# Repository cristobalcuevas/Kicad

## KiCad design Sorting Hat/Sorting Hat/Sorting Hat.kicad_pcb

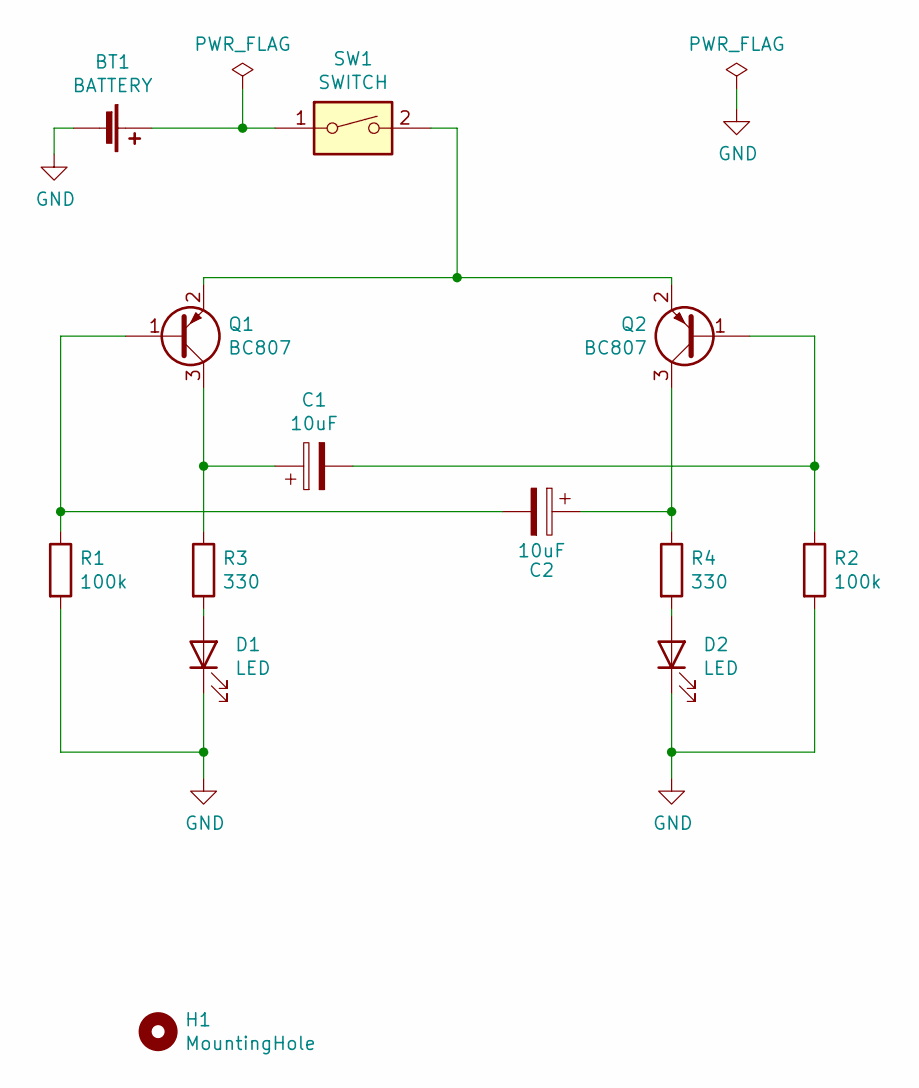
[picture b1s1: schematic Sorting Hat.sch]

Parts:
BT1: BATTERY; MPD_BK-912-TR
C1, C2: 10uF; CP_Elec_4x5.4
D1, D2: LED; D_1206_3216Metric_Pad1.42x1.75mm_HandSolder
H1: MountingHole; MountingHole_2.2mm_M2
Q1, Q2: BC807; SOT-23
R1, R2: 100k; R_1206_3216Metric_Pad1.42x1.75mm_HandSolder
R3, R4: 330; R_1206_3216Metric_Pad1.42x1.75mm_HandSolder
SW1: SWITCH; A6S-1104-H

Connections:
GND: BT1.2 (-), D1.1 (K), D2.1 (K), R1.2, R2.2
unnamed: BT1.1 (+), SW1.1
unnamed: C1.1, Q1.3 (C), R3.1
unnamed: C1.2, Q2.1 (B), R2.1
unnamed: C2.1, Q2.3 (C), R4.1
unnamed: C2.2, Q1.1 (B), R1.1
unnamed: D1.2 (A), R3.2
unnamed: D2.2 (A), R4.2
unnamed: Q1.2 (E), Q2.2 (E), SW1.2

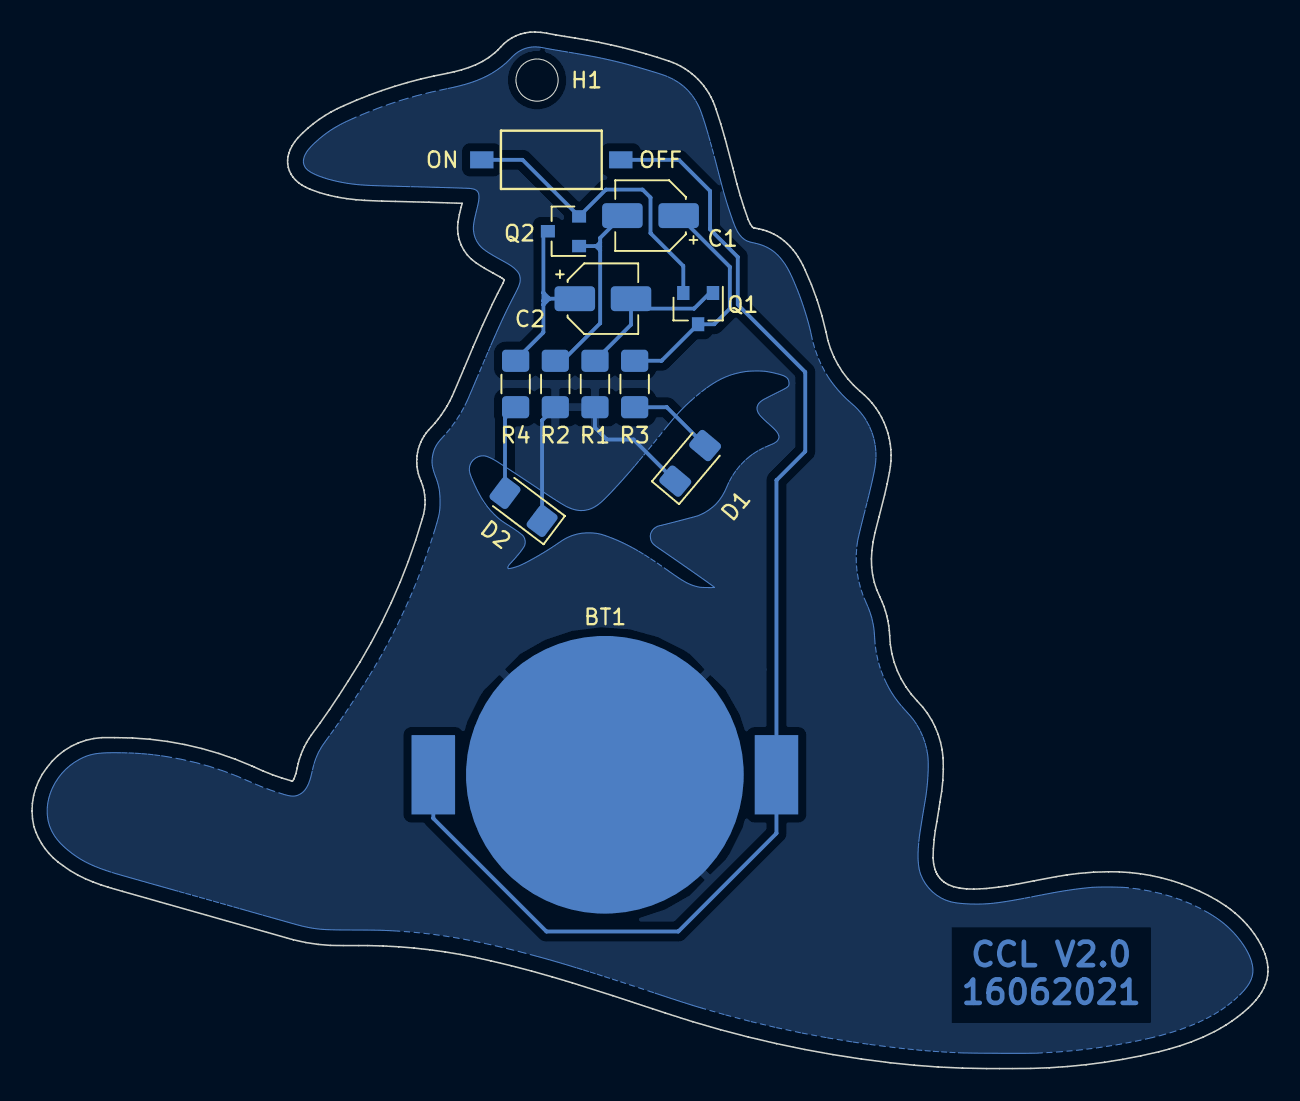
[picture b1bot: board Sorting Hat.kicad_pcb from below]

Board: 2 copper layers, 79.1 x 66.4 mm, 13 parts (12 on the bottom side), 9 nets.

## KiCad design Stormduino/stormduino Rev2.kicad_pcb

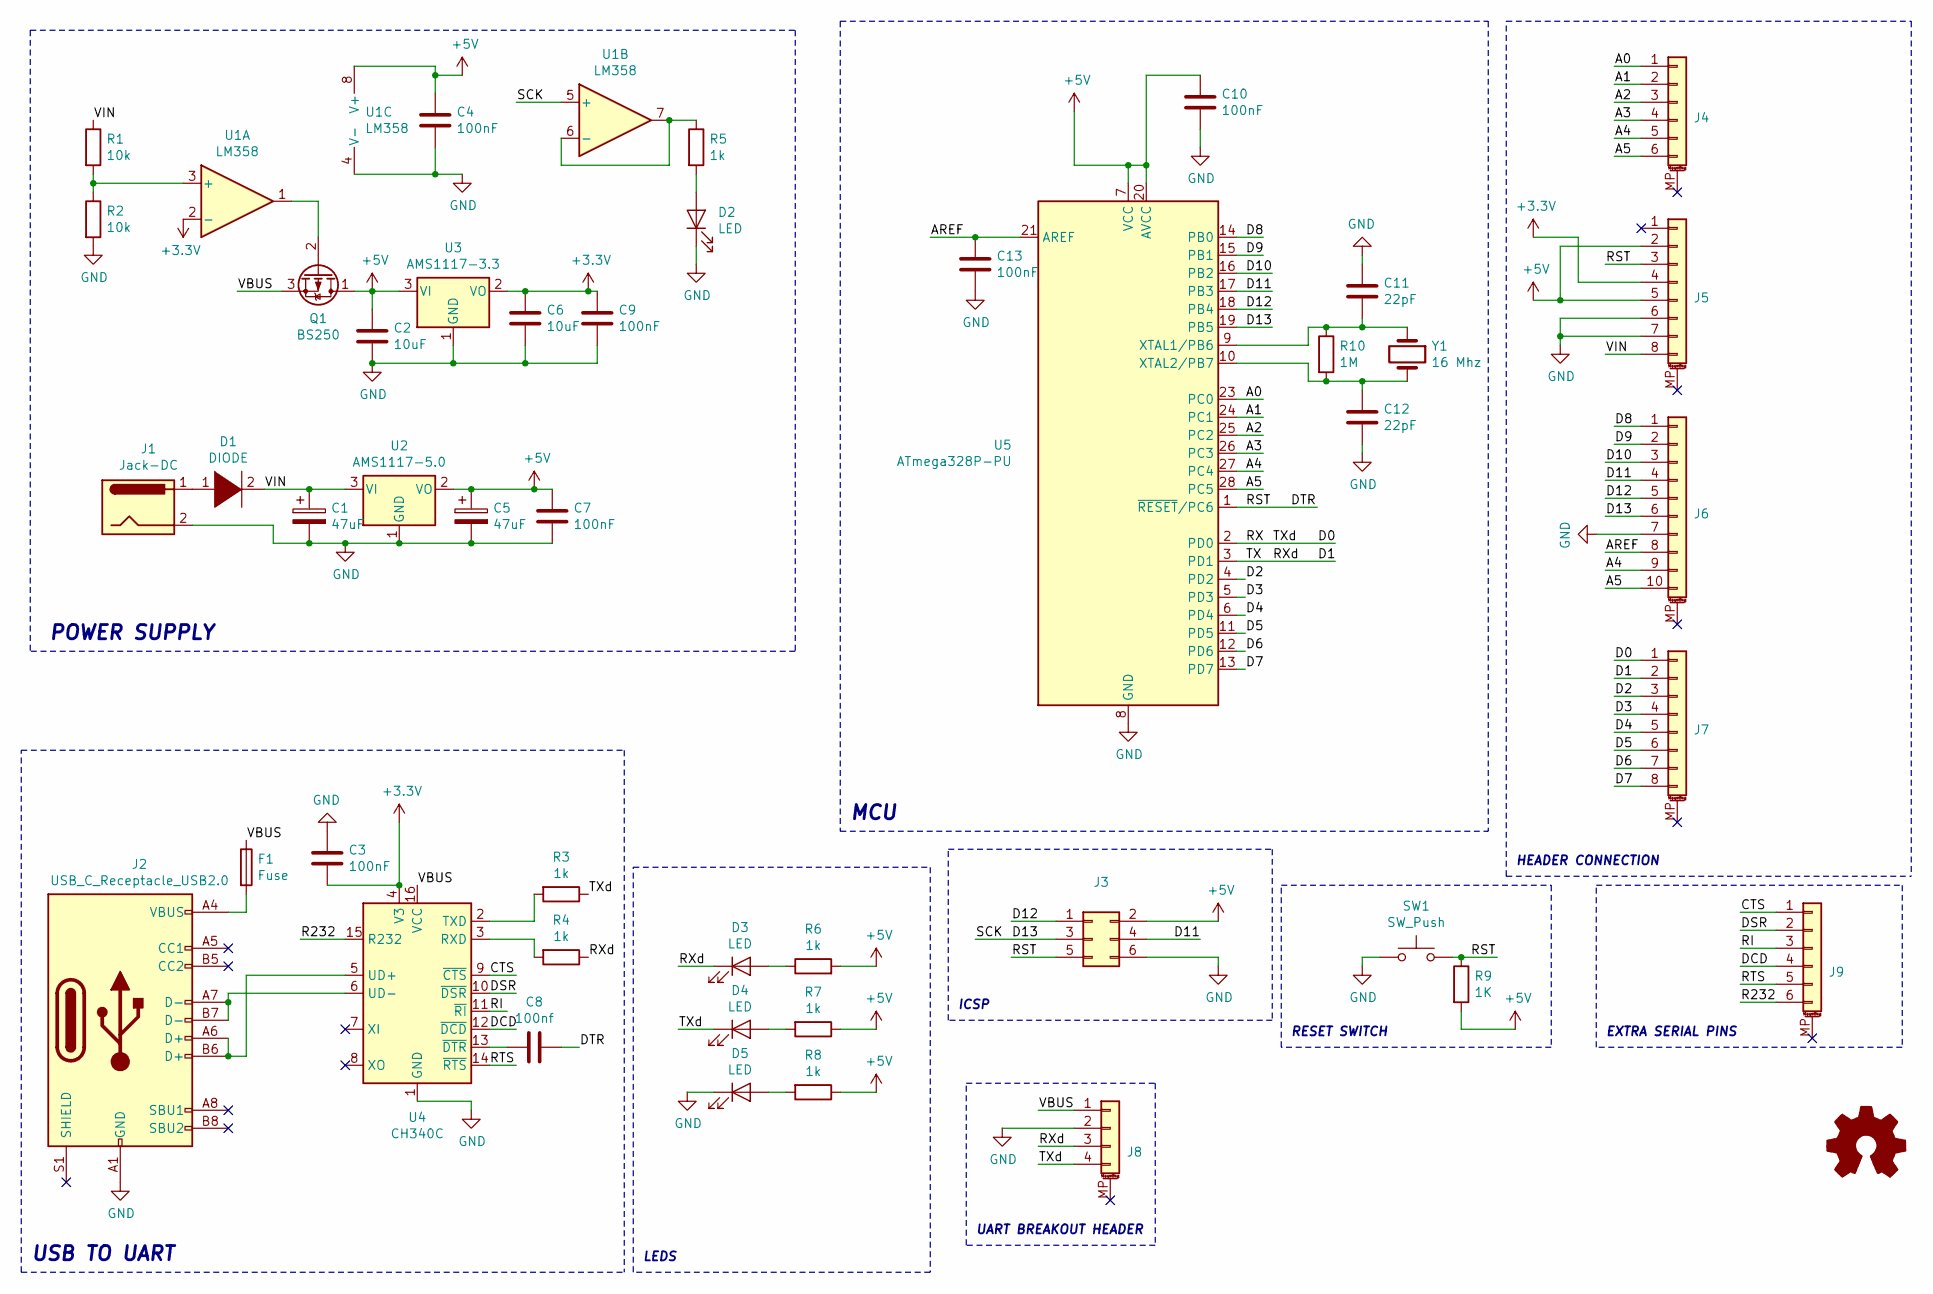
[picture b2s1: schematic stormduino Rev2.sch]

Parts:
C1, C5: 47uF
C2, C6: 10uF
C3, C4, C7, C9, C10, C13: 100nF
C8: 100nf
C11, C12: 22pF
D1: DIODE
D2, D3, D4, D5: LED
F1: Fuse
J1: Jack-DC
J2: USB_C_Receptacle_USB2.0
J3: Conn_02x03_Odd_Even
J4, J9: Conn_01x06_MountingPin
J5, J7: Conn_01x08_MountingPin
J6: Conn_01x10_MountingPin
J8: Conn_01x04_MountingPin
Q1: BS250; TO-92_Inline
R1, R2: 10k
R3, R4, R5, R6, R7, R8: 1k
R9: 1K
R10: 1M
SW1: SW_Push
U1: LM358
U2: AMS1117-5.0; SOT-223-3_TabPin2
U3: AMS1117-3.3; SOT-223-3_TabPin2
U4: CH340C; SOIC-16_3.9x9.9mm_P1.27mm
U5: ATmega328P-PU; DIP-28_W7.62mm
Y1: 16 Mhz

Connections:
+3V3: C3.2, C6.1, C9.1, J5.4, U1.2 (-), U3.2 (VO), U4.4 (V3)
/A0: J4.1, U5.23 (PC0)
/A1: J4.2, U5.24 (PC1)
/A2: J4.3, U5.25 (PC2)
/A3: J4.4, U5.26 (PC3)
/A4: J4.5, J6.9, U5.27 (PC4)
/A5: J4.6, J6.10, U5.28 (PC5)
/AREF: C13.1, J6.8, U5.21 (AREF)
/CTS: J9.1, U4.9 (~CTS)
/D0: D4.1 (K), J7.1, J8.4, R3.1, U5.2 (PD0)
/D1: D3.1 (K), J7.2, J8.3, R4.1, U5.3 (PD1)
/D2: J7.3, U5.4 (PD2)
/D3: J7.4, U5.5 (PD3)
/D4: J7.5, U5.6 (PD4)
/D5: J7.6, U5.11 (PD5)
/D6: J7.7, U5.12 (PD6)
/D7: J7.8, U5.13 (PD7)
/D8: J6.1, U5.14 (PB0)
/D9: J6.2, U5.15 (PB1)
/D10: J6.3, U5.16 (PB2)
/D11: J3.4, J6.4, U5.17 (PB3)
/D12: J3.1, J6.5, U5.18 (PB4)
/D13: J3.3, J6.6, U1.5 (+), U5.19 (PB5)
/DCD: J9.4, U4.12 (~DCD)
/DSR: J9.2, U4.10 (~DSR)
/DTR: C8.1, J3.5, J5.3, R9.1, SW1.2, U5.1 (~RESET~/PC6)
/R232: J9.6, U4.15 (R232)
/RI: J9.3, U4.11 (~RI)
/RTS: J9.5, U4.14 (~RTS)
/VBUS: F1.1, J8.1, Q1.3 (S), U4.16 (VCC)
/VIN: C1.1, D1.2 (A), J5.8, R1.1, U2.3 (VI)
GND: C1.2, C2.2, C3.1, C4.2, C5.2, C6.2, C7.2, C9.2, C10.2, C11.1, C12.2, C13.2, D2.1 (K), D5.1 (K), J1.2, J2.A1 (GND), J2.A12 (GND), J2.B1 (GND), J2.B12 (GND), J3.6, J5.6, J5.7, J6.7, J8.2, R2.2, SW1.1, U1.4 (V-), U2.1 (GND), U3.1 (GND), U4.1 (GND), U5.8 (GND), U5.22 (GND); also elsewhere on the board
unnamed: C8.2, U4.13 (~DTR)
unnamed: C11.2, R10.1, U5.9 (XTAL1/PB6), Y1.1
unnamed: C12.1, R10.2, U5.10 (XTAL2/PB7), Y1.2
unnamed: D1.1 (K), J1.1
unnamed: D2.2 (A), R5.2
unnamed: D3.2 (A), R6.1
unnamed: D4.2 (A), R7.2
unnamed: D5.2 (A), R8.2
unnamed: F1.2, J2.A4 (VBUS), J2.A9 (VBUS), J2.B4 (VBUS), J2.B9 (VBUS)
unnamed: J2.A6 (D+), J2.B6 (D+), U4.5 (UD+)
unnamed: J2.A7 (D-), J2.B7 (D-), U4.6 (UD-)
unnamed: R1.2, R2.1, U1.3 (+)
unnamed: R3.2, U4.2 (TXD)
unnamed: R4.2, U4.3 (RXD)
unnamed: R5.1, U1.6 (-), U1.7

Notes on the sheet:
POWER SUPPLY
USB TO UART
MCU
ICSP
HEADER CONNECTION
LEDS
RESET SWITCH
UART BREAKOUT HEADER
EXTRA SERIAL PINS

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
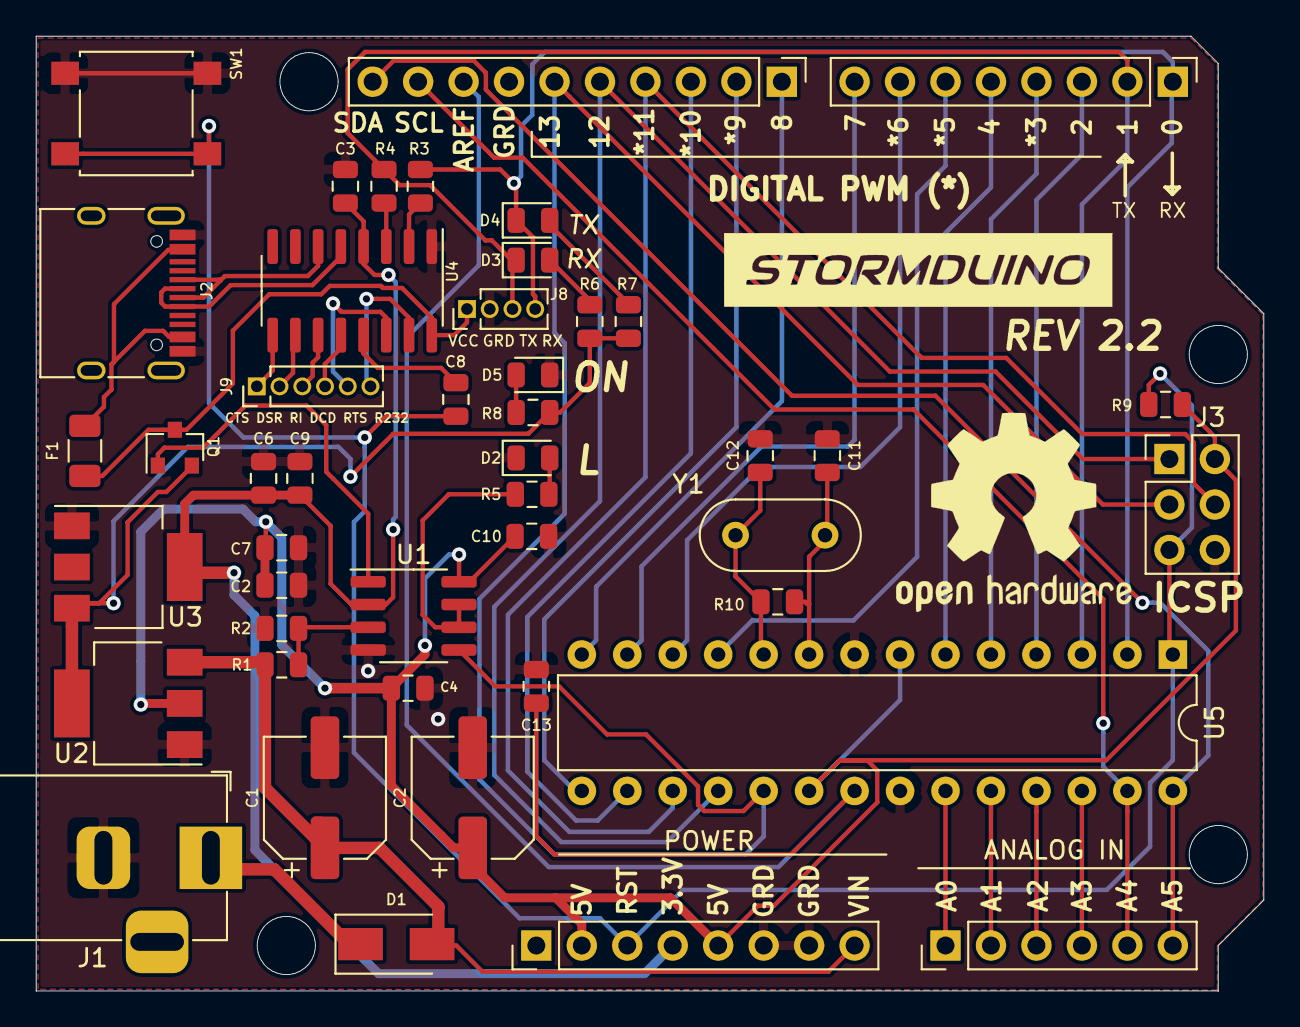
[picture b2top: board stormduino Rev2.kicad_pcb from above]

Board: 2 copper layers, 68.6 x 53.3 mm, 46 parts (0 on the bottom side), 49 nets.

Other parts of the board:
C2#2: 10uF; C_0805_2012Metric

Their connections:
GND: C2#2.2; also elsewhere on the board

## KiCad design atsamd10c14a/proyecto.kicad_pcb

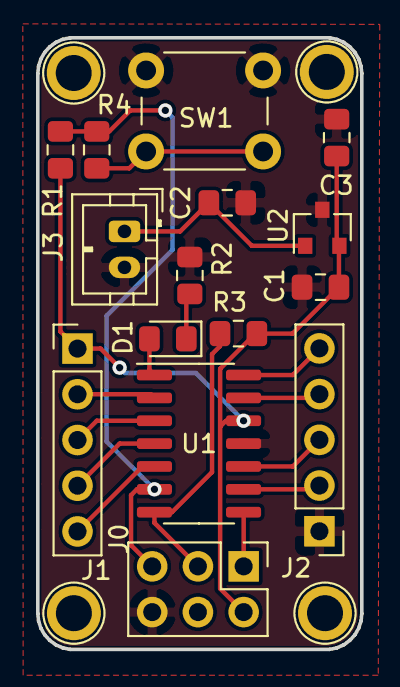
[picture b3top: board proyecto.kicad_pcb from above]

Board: 2 copper layers, 18.0 x 34.0 mm, 15 parts (0 on the bottom side), 17 nets.

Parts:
C1: 0.1uF; C_0805_2012Metric_Pad1.15x1.40mm_HandSolder
C2, C3: 1uF; C_0805_2012Metric_Pad1.15x1.40mm_HandSolder
D1: LED; LED_0805_2012Metric_Pad1.15x1.40mm_HandSolder
J0: SWD_PGM; PinHeader_2x03_P2.54mm_Vertical
J1: GPIO_A; PinHeader_1x05_P2.54mm_Vertical
J2: GPIO_B; PinHeader_1x05_P2.54mm_Vertical
J3: Battery; JST_PH_B2B-PH-K_1x02_P2.00mm_Vertical
R1: 10k; R_0805_2012Metric_Pad1.15x1.40mm_HandSolder
R2, R3: 1k; R_0805_2012Metric_Pad1.15x1.40mm_HandSolder
R4: 330R; R_0805_2012Metric_Pad1.15x1.40mm_HandSolder
SW1: SW_Push; SW_PUSH_6mm
U1: ATSAMD10C14A-SS; SOIC-14_3.9x8.7mm_P1.27mm
U2: AP7333-33SRG-7; SOT-23

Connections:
+3V3: C1.1, C3.1, J0.2, J1.1, R1.1, R3.2, U1.12, U2.2
+BATT: C2.1, J3.1, U2.1
GND: C1.2, C2.2, C3.2, J0.6, J2.1, J3.2, R2.2, SW1.2, U1.11, U2.3
GPIO_1: J1.2, U1.2
GPIO_2: J1.3, U1.3
GPIO_3: J1.4, U1.4
GPIO_4: J1.5, U1.5
GPIO_5: J2.5, U1.14
GPIO_6: J2.4, U1.13
GPIO_7: J2.3, U1.10
GPIO_8: J2.2, U1.9
LED: D1.2, U1.1
unnamed: D1.1, R2.1
unnamed: R4.1, SW1.1
SWCLK: J0.3, R3.1, U1.7
SWDIO: J0.1, U1.8
reset: J0.5, R1.2, R4.2, U1.6

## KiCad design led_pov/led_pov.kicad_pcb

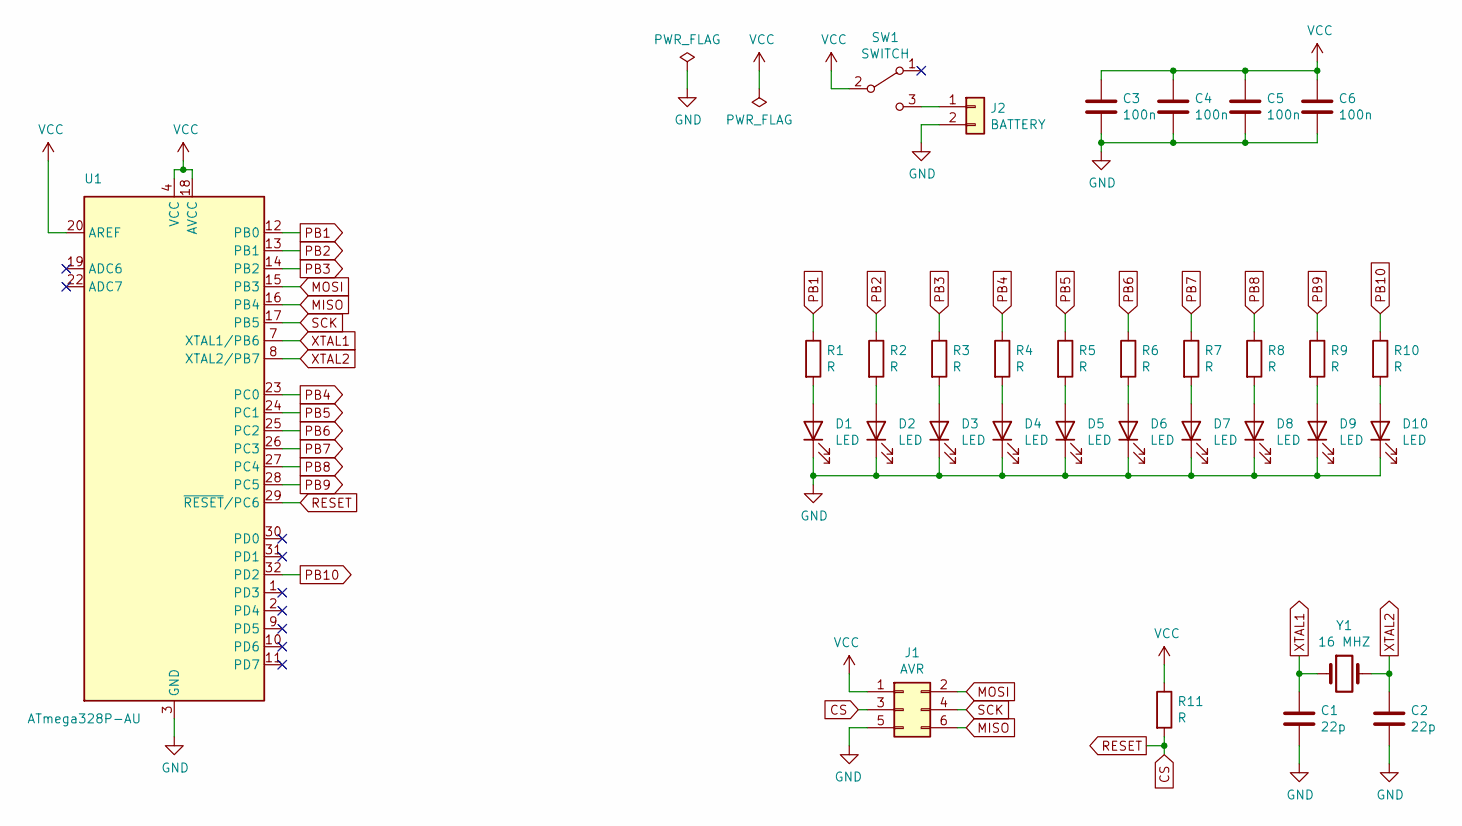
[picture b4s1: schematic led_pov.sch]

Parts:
C1, C2: 22p; C_1206_3216Metric
C3, C4, C5, C6: 100n; C_1206_3216Metric
D1, D2, D3, D4, D5, D6, D7, D8, D9, D10: LED; LED_1206_3216Metric
J1: AVR; PinHeader_2x03_P2.54mm_Vertical
J2: BATTERY; PinHeader_1x02_P2.54mm_Vertical
R1, R2, R3, R4, R5, R6, R7, R8, R9, R10, R11: R; R_1206_3216Metric
SW1: SWITCH; SW_SPDT_PCM12
U1: ATmega328P-AU; TQFP-32_7x7mm_P0.8mm
Y1: 16 MHZ; Crystal_HC49-4H_Vertical

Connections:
CS: J1.3, R11.2, U1.29 (~RESET~/PC6)
GND: C1.2, C2.2, C3.2, C4.2, C5.2, C6.2, D1.1 (K), D2.1 (K), D3.1 (K), D4.1 (K), D5.1 (K), D6.1 (K), D7.1 (K), D8.1 (K), D9.1 (K), D10.1 (K), J1.5, J2.2, U1.3 (GND), U1.5 (GND), U1.21 (GND)
MISO: J1.6, U1.16 (PB4)
MOSI: J1.2, U1.15 (PB3)
unnamed: D1.2 (A), R1.2
unnamed: D2.2 (A), R2.2
unnamed: D3.2 (A), R3.2
unnamed: D4.2 (A), R4.2
unnamed: D5.2 (A), R5.2
unnamed: D6.2 (A), R6.2
unnamed: D7.2 (A), R7.2
unnamed: D8.2 (A), R8.2
unnamed: D9.2 (A), R9.2
unnamed: D10.2 (A), R10.2
unnamed: J2.1, SW1.3 (C)
PB1: R1.1, U1.12 (PB0)
PB2: R2.1, U1.13 (PB1)
PB3: R3.1, U1.14 (PB2)
PB4: R4.1, U1.23 (PC0)
PB5: R5.1, U1.24 (PC1)
PB6: R6.1, U1.25 (PC2)
PB7: R7.1, U1.26 (PC3)
PB8: R8.1, U1.27 (PC4)
PB9: R9.1, U1.28 (PC5)
PB10: R10.1, U1.32 (PD2)
SCK: J1.4, U1.17 (PB5)
VCC: C3.1, C4.1, C5.1, C6.1, J1.1, R11.1, SW1.2 (B), U1.4 (VCC), U1.6 (VCC), U1.18 (AVCC), U1.20 (AREF)
XTAL1: C1.1, U1.7 (XTAL1/PB6), Y1.1
XTAL2: C2.1, U1.8 (XTAL2/PB7), Y1.2

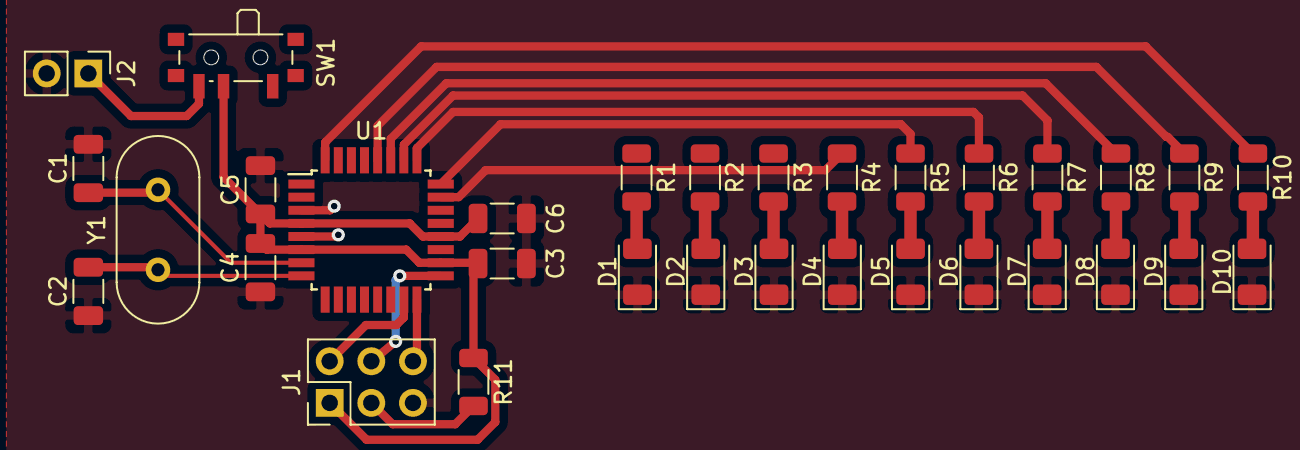
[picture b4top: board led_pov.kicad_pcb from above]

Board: 2 copper layers, 32 parts (0 on the bottom side), 29 nets.

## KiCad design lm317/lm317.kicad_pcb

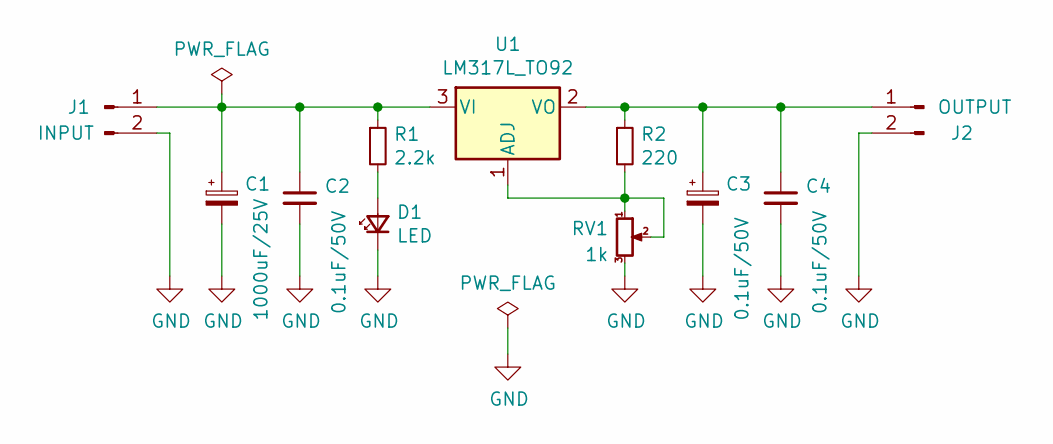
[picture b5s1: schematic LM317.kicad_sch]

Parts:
C1: 1000uF/25V; CP_Elec_10x12.5
C2, C4: 0.1uF/50V; C_0805_2012Metric
C3: 0.1uF/50V; CP_Elec_5x5.4
D1: LED; LED_0805_2012Metric_Castellated
J1: INPUT; Molex_KK-254_AE-6410-02A_1x02_P2.54mm_Vertical
J2: OUTPUT; Molex_KK-254_AE-6410-02A_1x02_P2.54mm_Vertical
R1: 2.2k; R_0805_2012Metric
R2: 220; R_0805_2012Metric
RV1: 1k; Potentiometer_Bourns_3224W_Vertical
U1: LM317L_TO92; TO-252-3_TabPin2

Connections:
GND: C1.2, C2.2, C3.2, C4.2, D1.1 (K), J1.2, J2.2, RV1.3
unnamed: C1.1, C2.1, J1.1, R1.1, U1.3 (VI)
unnamed: C3.1, C4.1, J2.1, R2.1, U1.2 (VO)
unnamed: D1.2 (A), R1.2
unnamed: R2.2, RV1.1, RV1.2, U1.1 (ADJ)

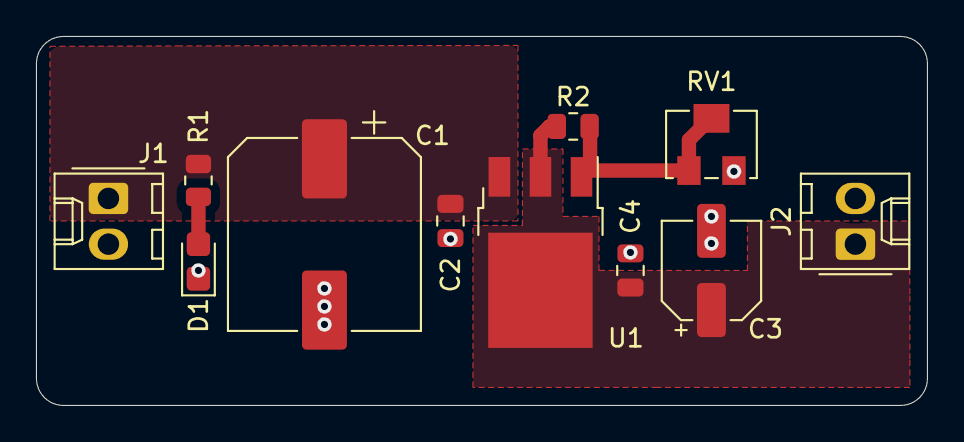
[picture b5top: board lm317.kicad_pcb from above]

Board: 2 copper layers, 49.5 x 20.5 mm, 11 parts (0 on the bottom side), 5 nets.

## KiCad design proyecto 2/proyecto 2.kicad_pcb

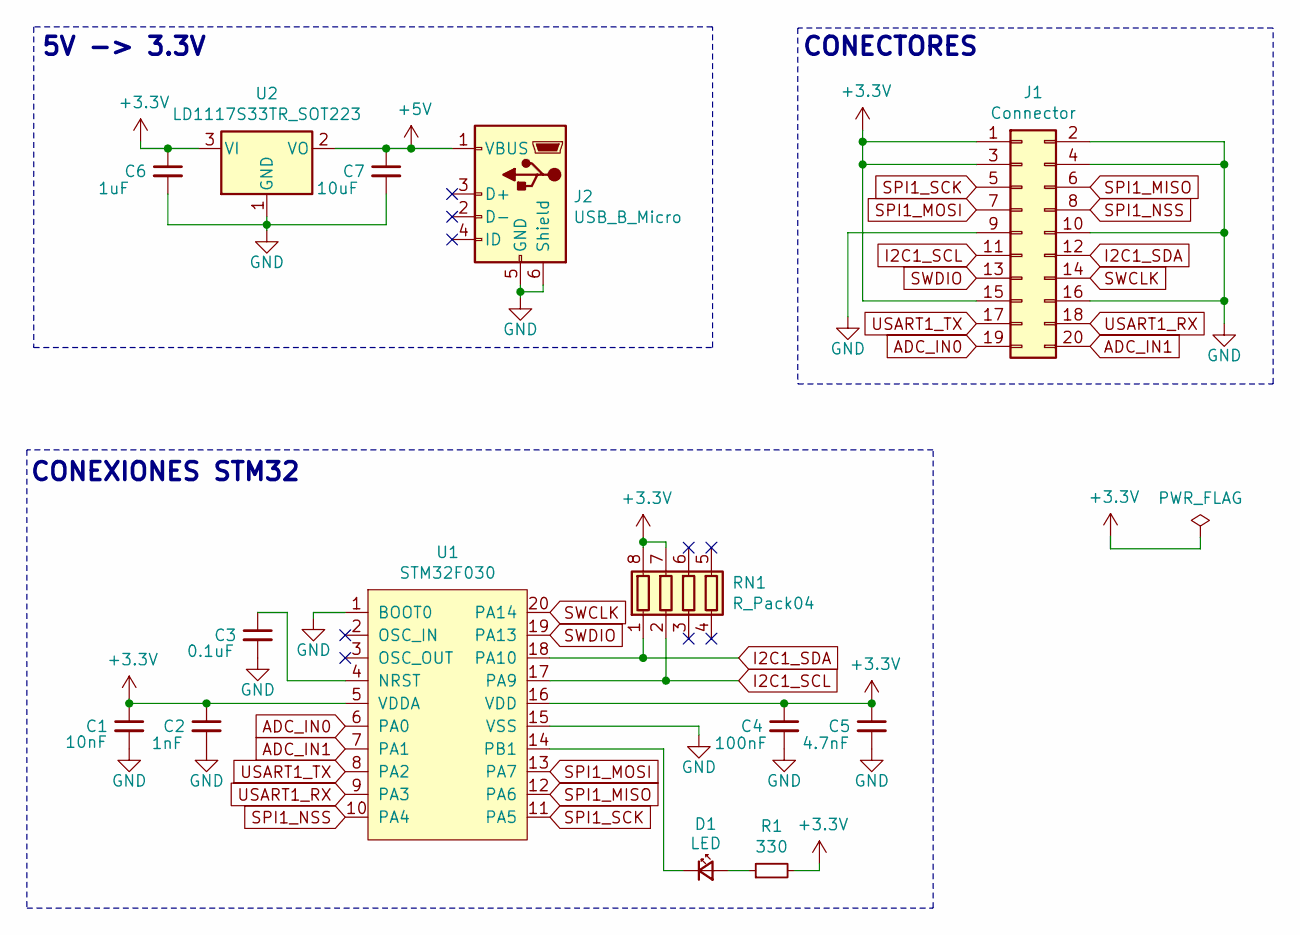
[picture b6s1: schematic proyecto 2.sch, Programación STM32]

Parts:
C1: 10nF; C_0805_2012Metric_Pad1.15x1.40mm_HandSolder
C2: 1nF; C_0805_2012Metric_Pad1.15x1.40mm_HandSolder
C3: 0.1uF; C_0805_2012Metric_Pad1.15x1.40mm_HandSolder
C4: 100nF; C_0805_2012Metric_Pad1.15x1.40mm_HandSolder
C5: 4.7nF; C_0805_2012Metric_Pad1.15x1.40mm_HandSolder
C6: 1uF; C_0805_2012Metric_Pad1.15x1.40mm_HandSolder
C7: 10uF; C_0805_2012Metric_Pad1.15x1.40mm_HandSolder
D1: LED; LED_0805_2012Metric_Pad1.15x1.40mm_HandSolder
J1: Connector; PinHeader_2x10_P2.54mm_Vertical
J2: USB_B_Micro; USB_Micro-B_Molex-105017-0001
R1: 330; R_0805_2012Metric_Pad1.15x1.40mm_HandSolder
RN1: R_Pack04; R_Array_Convex_4x0603
U1: STM32F030; TSSOP-20_4.4x6.5mm_P0.65mm
U2: LD1117S33TR_SOT223; SOT-223-3_TabPin2

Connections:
+3V3: C1.1, C2.1, C4.1, C5.1, C6.1, J1.1, J1.3, J1.15, R1.2, RN1.7 (R2.2), RN1.8 (R1.2), U1.5 (VDDA), U1.16 (VDD), U2.3 (VI)
+5V: C7.1, J2.1 (VBUS), U2.2 (VO)
ADC_IN0: J1.19, U1.6 (PA0)
ADC_IN1: J1.20, U1.7 (PA1)
GND: C1.2, C2.2, C3.2, C4.2, C5.2, C6.2, C7.2, J1.2, J1.4, J1.9, J1.10, J1.16, J2.5 (GND), J2.6 (Shield), U1.1 (BOOT0), U1.15 (VSS), U2.1 (GND)
I2C1_SCL: J1.11, RN1.2 (R2.1), U1.17 (PA9)
I2C1_SDA: J1.12, RN1.1 (R1.1), U1.18 (PA10)
unnamed: C3.1, U1.4 (NRST)
unnamed: D1.1 (K), U1.14 (PB1)
unnamed: D1.2 (A), R1.1
SPI1_MISO: J1.6, U1.12 (PA6)
SPI1_MOSI: J1.7, U1.13 (PA7)
SPI1_NSS: J1.8, U1.10 (PA4)
SPI1_SCK: J1.5, U1.11 (PA5)
SWCLK: J1.14, U1.20 (PA14)
SWDIO: J1.13, U1.19 (PA13)
USART1_RX: J1.18, U1.9 (PA3)
USART1_TX: J1.17, U1.8 (PA2)

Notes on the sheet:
5V -> 3.3V
CONECTORES
CONEXIONES STM32

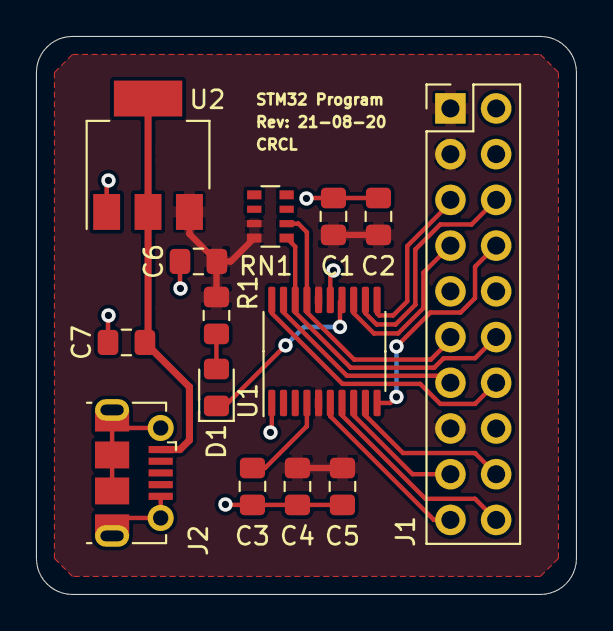
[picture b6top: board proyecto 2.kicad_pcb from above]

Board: 2 copper layers, 30.0 x 31.0 mm, 14 parts (0 on the bottom side), 18 nets.
